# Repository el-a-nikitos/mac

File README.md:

mac
***
Плата-визитка на МК 1986ВЕ92

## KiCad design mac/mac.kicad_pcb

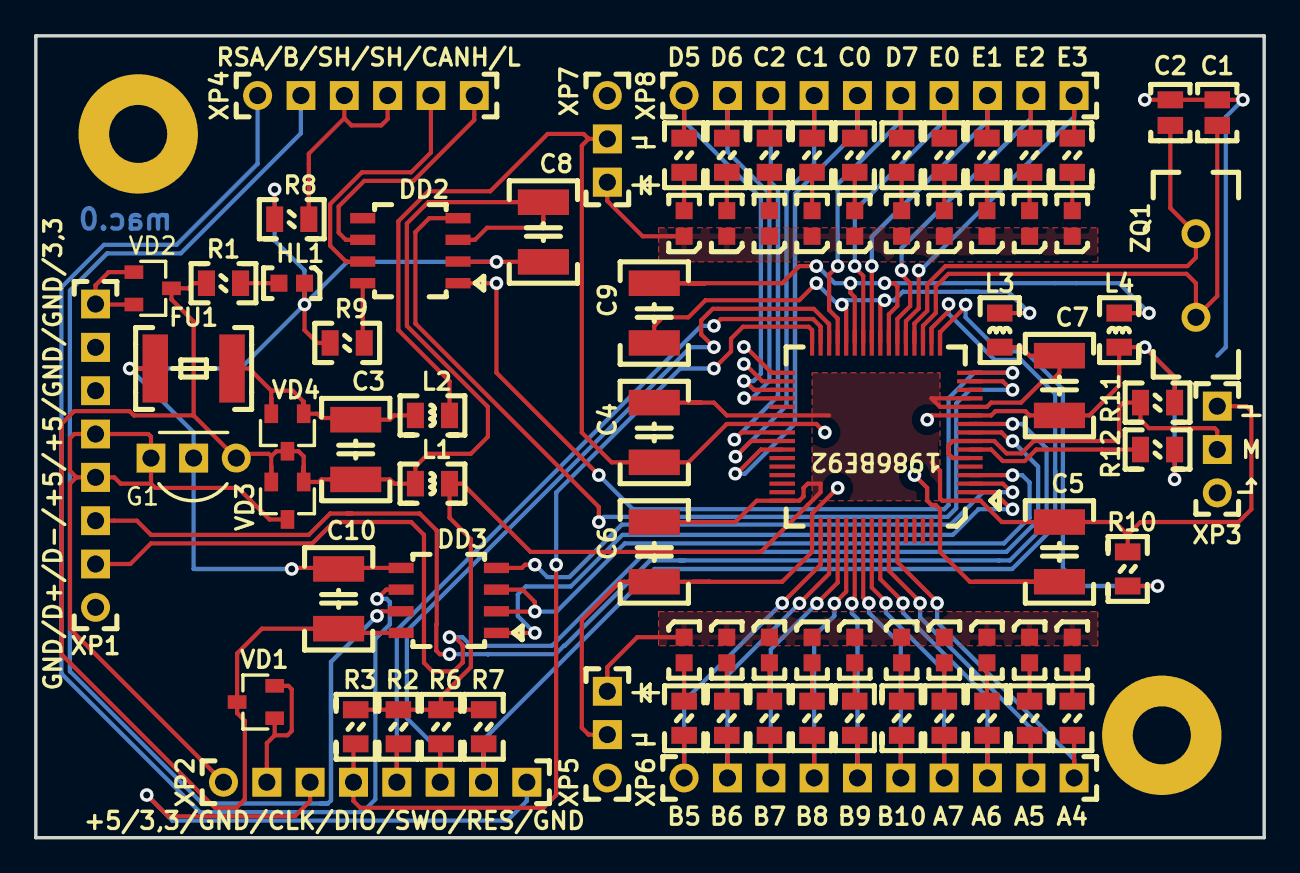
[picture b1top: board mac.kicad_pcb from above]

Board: 2 copper layers, 72.0 x 47.0 mm, 85 parts (0 on the bottom side), 75 nets.

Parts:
C1, C2: 12пФ(0603); Конденсатор_SMD_0603
C3, C4, C5, C6, C7, C8, C9, C10: 4,7мкФ(1210); Конденсатор_SMD_1210
DD1: 1986ВЕ92QL; Микросхема_1986ВЕ92QL
DD2: 5559ИН14А(CAN); SO-8
DD3: 5559ИН10_28(UART-RS485); SO-8
FU1: Предохранитель; Предохранитель_SMD_1812
G1: стабилизатор_нерегулируемый_LM2950; Стабилизатор_корпус_TO-92
HL1, HL2, HL3, HL4, HL5, HL6, HL7, HL8, HL9, HL10, HL11, HL12, HL13, HL14, HL15, HL16, HL17, HL18, HL19, HL20, HL21: Светодиод; Светодиод_SMD_0603
L1, L2, L3, L4: 33мкГн(0805); Чип-индуктивность_SMD_0805
M3, M3#2: Отверстие_М3
R1, R14, R15, R16, R17, R18, R19, R20, R21, R22, R23, R24, R25, R26, R27, R28, R29, R30, R31, R32, R33: 39; Резистор_SMD_0805_0,125Вт
R2, R3, R6, R7, R10, R11, R12: 20к; Резистор_SMD_0805_0,125Вт
R8: 100к; Резистор_SMD_0805_0,125Вт
R9: 24к; Резистор_SMD_0805_0,125Вт
VD1, VD2, VD3, VD4: BAR43CFILM; Диод_BAR43CFILM_SOT-23
XP1, XP2: Вилка_PLS8; Вилка_PLS8_вертикальная
XP3, XP5, XP7: Вилка_PLS3; Вилка_PLS3_вертикальная
XP4: Вилка_PLS6; Вилка_PLS6_вертикальная
XP6, XP8: Вилка_PLS10; Вилка_PLS10_вертикальная
ZQ1: 16М; Резонатор_РК456МДУ(DIP)

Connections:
/+3,3: VD2.1, XP1.8
/+3,3_prog: VD1.1, XP2.2
/+4...30: G1.3, VD3.2, XP1.4, XP1.5, XP2.1
/A_GND_MC: C9.2, DD1.23, DD1.27, L4.2
/A_VCC_MC: C9.1, DD1.24, DD1.28, L3.2
/CAN_H: DD2.7, XP4.5
/CAN_L: DD2.6, XP4.6
/GND: C8.1, C10.1, DD2.2, DD3.5, FU1.1, G1.2, HL1.2, R8.1, R9.1, XP1.1, XP1.6, XP1.7, XP2.3, XP2.8
/GND_LED1: HL2.2, HL3.2, HL4.2, HL5.2, HL6.2, HL7.2, HL8.2, HL9.2, HL10.2, HL11.2, XP5.3
/GND_LED2: HL12.2, HL13.2, HL14.2, HL15.2, HL16.2, HL17.2, HL18.2, HL19.2, HL20.2, HL21.2, XP7.3
/GND_MC: C1.2, C2.2, C4.2, C5.2, C6.2, C7.2, DD1.11, DD1.39, DD1.49, DD1.64, L2.2, L4.1, R11.2, R12.2, XP3.1, XP5.2, XP7.2
/MODE: DD1.6, DD1.8, R11.1, XP3.2
/PA4: DD1.59, R23.2, XP6.10
/PA5: DD1.58, R22.2, XP6.9
/PA6: DD1.57, R21.2, XP6.8
/PA7: DD1.56, R20.2, XP6.7
/PB5: DD1.50, R14.2, XP6.1
/PB6: DD1.51, R15.2, XP6.2
/PB7: DD1.52, R16.2, XP6.3
/PB8: DD1.53, R17.2, XP6.4
/PB9: DD1.54, R18.2, XP6.5
/PB10: DD1.55, R19.2, XP6.6
/PC0_SCL1: DD1.42, R28.2, XP8.5
/PC1_SDA1: DD1.41, R27.2, XP8.4
/PC2: DD1.40, R26.2, XP8.3
/PD5_ADC5: DD1.35, R24.2, XP8.1
/PD6_ADC6: DD1.36, R25.2, XP8.2
/PD7_ADC7: DD1.29, R29.2, XP8.6
/PE0_T2C1_DAC: DD1.26, R30.2, XP8.7
/PE1_T2nC1: DD1.25, R31.2, XP8.8
/PE2_T2C3: DD1.22, R32.2, XP8.9
/PE3_T2nC3: DD1.21, R33.2, XP8.10
/PE6_C2-RX: DD1.16, DD2.1
/PE6_C2-TX: DD1.15, DD2.4
/PF0_U2-RX: DD1.2, DD3.1
/PF1_U2-TX: DD1.3, DD3.4
/PF2_U2-En: DD1.4, DD3.2, DD3.3
/RES: DD1.18, R7.2, XP2.7
/RS_A: DD3.6, XP4.1
/RS_B: DD3.7, XP4.2
/TCK_CLK_TX: DD1.32, R3.2, XP2.4
/TDO_SWO: DD1.30, R6.2, XP2.6
/TMS_DIO_RX: DD1.31, R2.2, XP2.5
/USB_D+: DD1.9, XP1.2
/USB_D-: DD1.10, XP1.3
/VCC: C3.1, C8.2, C10.2, DD2.3, DD3.8, G1.1, L1.1, R1.2, VD1.2, VD2.2, VD3.1, VD4.2
/VCC_MC: C4.1, C5.1, C6.1, C7.1, DD1.1, DD1.12, DD1.13, DD1.38, DD1.48, L1.2, L3.1, R2.1, R3.1, R6.1, R7.1, R10.1, XP3.3
unnamed: C1.1, DD1.19, ZQ1.1
unnamed: C2.1, DD1.20, ZQ1.2
unnamed: C3.2, FU1.2, L2.1, VD4.1
unnamed: DD1.7, R12.1
unnamed: DD1.17, R10.2
unnamed: DD2.8, R9.2
unnamed: HL1.1, R1.1
unnamed: HL2.1, R14.1
unnamed: HL3.1, R15.1
unnamed: HL4.1, R16.1
unnamed: HL5.1, R17.1
unnamed: HL6.1, R18.1
unnamed: HL7.1, R19.1
unnamed: HL8.1, R20.1
unnamed: HL9.1, R21.1
unnamed: HL10.1, R22.1
unnamed: HL11.1, R23.1
unnamed: HL12.1, R24.1
unnamed: HL13.1, R25.1
unnamed: HL14.1, R26.1
unnamed: HL15.1, R27.1
unnamed: HL16.1, R28.1
unnamed: HL17.1, R29.1
unnamed: HL18.1, R30.1
unnamed: HL19.1, R31.1
unnamed: HL20.1, R32.1
unnamed: HL21.1, R33.1
unnamed: R8.2, XP4.3, XP4.4

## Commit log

2019-01-05 создан проект
    -на схеме расставлена схема питания, сброса, программирования
    -не выведен USB
    -не расставлены посадочные места
    -не выводились DIO
2019-01-06 -выведен USB
    -добавлены метки DIO
    -не проверено, все ли расставлены посадочные места
2019-01-06 на схеме (-), на трассировке (*)
    -поставлен uart-rs485
    -поставлена микросхема CAN
    -CAN и RS выведены наружу
    -выводные разъемы
    *определен максимальный габарит 45х70
2019-01-06 трассировка в самом разгаре
    выведены GPIO
    не выведены ответвления на RS и CAN
    не выведено программирование
    не разведена земля
2019-01-06 закончена разводка, не проводилась стилистическая проверка
2019-01-07 причесывание
    -изменен габарит: 72х47 мм
    -добавлены заливки земли на обратной стороне
    -переходные отверстия вынесены за пределы контактных площадок
    -прототип рекламки шелкографией
2019-01-30 добавлен номер телефона, исправлено положение стабилизатора
2019-02-10 откорректирована надпись, перенесен id + добавлены gerber-файлы
2019-09-27 "mac" версия 1
2019-09-27 не размещены вилки, определен габарит
